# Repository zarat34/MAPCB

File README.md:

# MAPCB
PCB pour ARDUINO Mini , alimentation par USB, alim moteur pas à pas
Ce repo contient le schematic et board pour un PCB conçu pour une arduino UNO 5 mini.
Il permet d'acceder aux differentes Piins avec des "pin heads" 
il permet d'alimenter un moteur pas à pas 
il prévoit :
plusieurs connections pour alimenter des capteurs(GND et VCC 5V)
les connections pour le programmateur de l'arduino
des connections pour une carte RFID 
des connections pour une carte wifi
des connection pour I2C (pins A4 et A5)
connection pour un  buzzer
connection pour une led

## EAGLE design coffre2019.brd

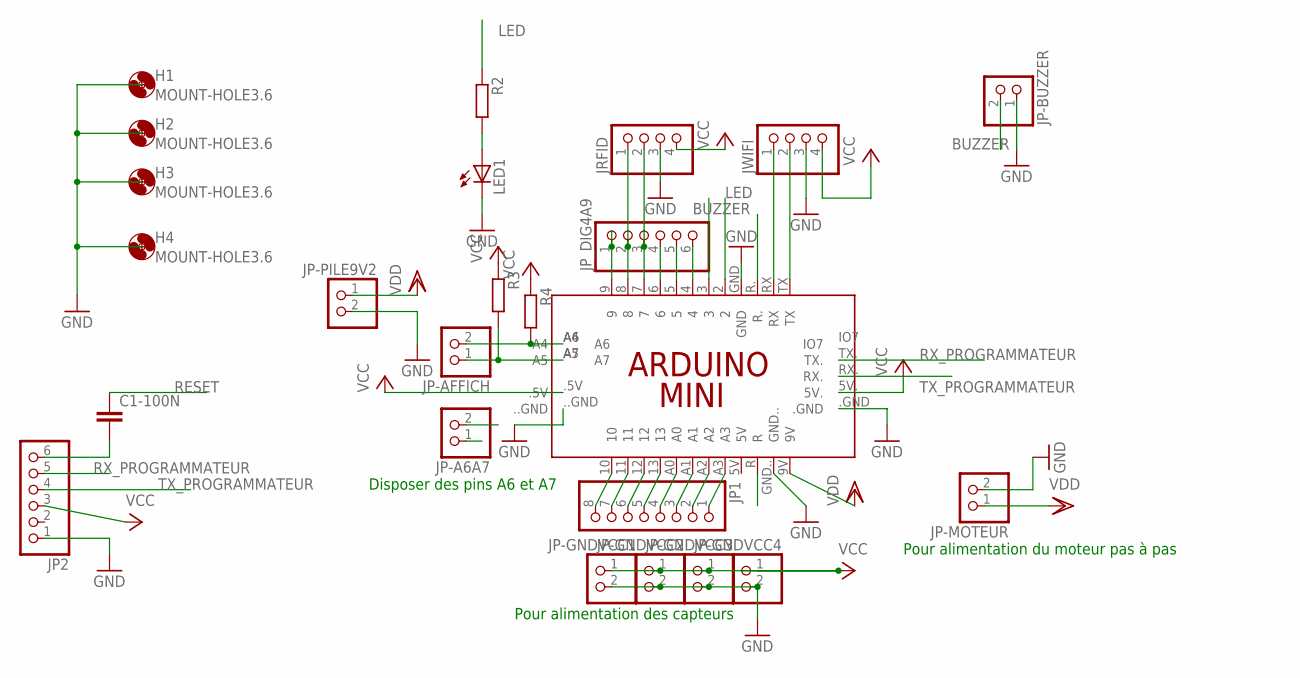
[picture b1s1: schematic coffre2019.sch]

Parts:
C1-100N: C5/3; C5B3
H1, H2, H3, H4: MOUNT-HOLE3.6; 3,6
JP1: PINHD-1X8; 1X08
JP2: PINHD-1X6; 1X06
JP-A6A7: PINHD-1X2; 1X02
JP-AFFICH: PINHD-1X2; 1X02
JP-BUZZER: PINHD-1X2; 1X02
JP-GNDVCC1, JP-GNDVCC2, JP-GNDVCC3, JP-GNDVCC4: PINHD-1X2; 1X02
JP-MOTEUR: PINHD-1X2; 1X02
JP-PILE9V2: PINHD-1X2; 1X02
JP_DIG4A9: PINHD-1X6; 1X06
JRFID: PINHD-1X4; 1X04
JWIFI: PINHD-1X4; 1X04
LED1: LED5MM
PCB1: ARDUINO_MINI
R2, R3, R4: R-EU_0207/10; 0207/10

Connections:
BUZZER: JP-BUZZER.2, PCB1.3
GND: JP2.1, JP-BUZZER.1, JP-GNDVCC1.2, JP-GNDVCC2.2, JP-GNDVCC3.2, JP-GNDVCC4.2, JP-MOTEUR.2, JP-PILE9V2.2, JRFID.3, JWIFI.3, LED1.K (C), PCB1...GND, PCB1..GND, PCB1.GND, PCB1.GND..
LED: PCB1.2, R2.1
unnamed: JP_DIG4A9.2, JRFID.1, PCB1.8
unnamed: JWIFI.1, PCB1.RX
unnamed: JP_DIG4A9.3, JRFID.2, PCB1.7
unnamed: JWIFI.2, PCB1.TX
unnamed: LED1.A, R2.2
unnamed: JP1.8, PCB1.10
unnamed: JP1.7, PCB1.11
unnamed: JP1.6, PCB1.12
unnamed: JP1.5, PCB1.13
unnamed: JP1.4, PCB1.A0
unnamed: JP1.3, PCB1.A1
unnamed: JP1.2, PCB1.A2
unnamed: JP1.1, PCB1.A3
unnamed: C1-100N.2, JP2.6
unnamed: JP_DIG4A9.6, PCB1.4
unnamed: JP_DIG4A9.5, PCB1.5
unnamed: JP_DIG4A9.4, PCB1.6
unnamed: JP-AFFICH.2, PCB1.A4, R4.2
unnamed: JP-AFFICH.1, PCB1.A5, R3.2
PIN9ARD: JP_DIG4A9.1, PCB1.9
RESET: C1-100N.1, PCB1.R.
RX_PROGRAMMATEUR: JP2.5, PCB1.TX.
TX_PROGRAMMATEUR: JP2.4, PCB1.RX.
VCC: JP2.3, JP-GNDVCC1.1, JP-GNDVCC2.1, JP-GNDVCC3.1, JP-GNDVCC4.1, JRFID.4, JWIFI.4, PCB1.5V., PCB1..5V, R3.1, R4.1
VDD: JP-PILE9V2.1, PCB1.9V
VERSA6: JP-A6A7.2
VERSA7: JP-A6A7.1

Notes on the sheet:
Pour alimentation des capteurs
Pour alimentation du moteur pas à pas
Disposer des pins A6 et A7

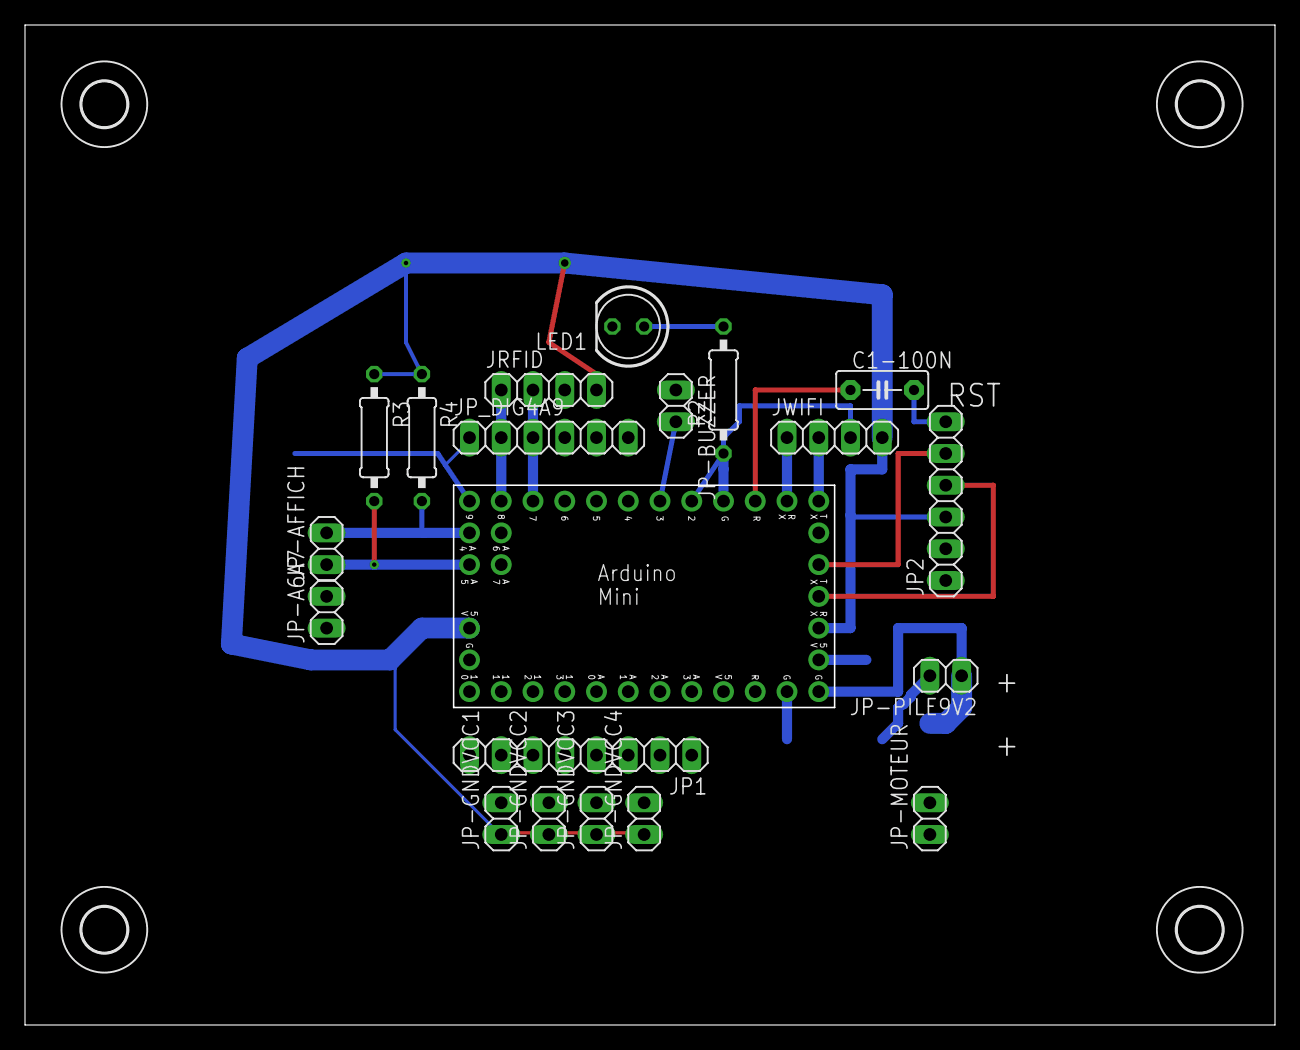
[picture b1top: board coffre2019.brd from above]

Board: 2 copper layers, 99.9 x 79.9 mm, 24 parts (0 on the bottom side), 28 nets.

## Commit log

2019-03-25 ajout schematic et board
